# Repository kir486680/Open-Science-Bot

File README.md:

# Open-Science-Bot

ACTIVE DEVELOPMENT

# Introduction
The emerging open science movement provides an opportunity to topple decades of scientific inequity by creating tools that enable engagement in science by underprivileged or marginalized communities. In this movement, scientific data, code, and knowledge, are shared openly in findable, accessible, interoperable, and reusable (F.A.I.R.) forms. However, it is not enough to make software and code available. Scientists need the opportunity to test their hypotheses in a way that increases their understanding while contributing to the broader scientific community.  

Take as an example, electrodeposition which is a method for coating a thin layer of one metal on top of a different metal to modify its surface properties. It is widely used industrially to create corrosion-resistant coatings for automobiles, improve electrical and thermal conductivity in electrical components, and manufacture screens. Optimizing the composition, surface finish, and density of an electroplated alloy is a tedious manual process that involves controlling the concentration of ions and surfactants, the cathodic current, and the temperature of the plating solution. State of the art autonomous deposition tools are currently only possible in well-funded research labs such as at NIST and NRC, where there are active projects within this space.

# Project Description
This research proposes a low-cost and open-source electrochemistry robot. The robot will be a platform for investigating electrochemistry at a price that is suitable for high school science labs but with sufficient precision and extensibility to benefit academic and industrial research.

The following robot has 
- lego xyz stage, which is controlled by Lego Mindstorm Inventor motors and brain, where two motors drive the x and y axes. The motor controlling the y-axis is on the cart carrying the end effectors. The two end effectors of the xyz stage that the cart carries have a gripper, a holder, and a tube connected to a pump. Both end effectors are controlled by another two Lego Mindstorm Inventor motors, and one of them carries the gripper used to grip metal samples and is actuated by a Hitech servo motor. The other end effector carries the reference electrode holder (you have to preinstall them manually), and a tube connected to a pump that pumps electrolytes from the beaker (currently connected to the two beakers).
- another pump connected to the chemical reactor used to drain the reactor after each experiment.
- chemical reactor where the counter electrode is preinstalled, and you are able to submerge the metal sample from the gripper, the preinstalled reference, and pump the liquid which are all held by the end-effector of the xyz stage described above. 
- a metal holder which simply holds the metal samples. 
- potentiostat which is controlled by the software. This is the biggest pain point of the project right now. You need to run the PSPythonSDK/MeasurementExample.py script in palmsdk folder on the windows laptop in order to get the data from the potentiostat. (when you are in the PSPythonSDK folder, just type ```python MeasurementExample.py```). If you want to run the experiment manually, you need to use the PSTrace app on windows. However, also keep in mind that in order to run the potentiostat script you need to use Python 3.8 or below. 

# Example

You can run examples/main.py, which is a preprogrammed sequence that does the following: (Keep in mind that the actual MeasurementExample.py needs to be run separately)
1. Pick up a piece of metal by moving the xyz stage over the metal holder, lower the gripper end effector over the piece of metal, gripping it, and then raise the end effector.
2. The xyz stage will be moved above the reactor, the end effector carrying the pump will be lowered, and the pump will pump some liquid into the reactor.
3. After enough liquid has been pumped into the reactor, the second end effector with the piece of metal will be lowered into the reactor. The experiment will begin.
4. After the experiment, both end effectors will be raised. The second pump will drain the liquid from the reactor.
5. The xyz stage will be moved to a nearby spot to drop off the metal sample. The xyz stage will then be moved back to the (0,0,0) location.

# What is next?

1. You need to be able to somehow call the MeasurementExample.py from the examples/main.py. For that, you might need to setup a server on the raspi using fastapi python package, and also run a server on the windows computer which could execute MeasurementExample.py. I was not able to find a direct way to run the potentiostat from the raspi, but it should be possible... So choose whatever option you think is worth your time.
2. Do active learning. Familiarize yourself with the active_learning/activeLearning.ipynb, and you can use this template code to set up a real system using the robot. The purpose of that demo is to see how you can autonomously find the concentration of electrolyte A and B to achieve a specific goal(in this example the goal is to run an experiment with a peak of 100mV as signified by ```if np.abs(Y_next - 100) < 1: ```)
3. Automate electrolyte replacement in the bath. I have already purchased a pump and Robert will be designing the 3D model for that. 

So what are the specific steps? 

1. find a specific electrochemical experiment that you want to be running(ask prof. Jae for that). Preferrably its some experiment where you are trying to find the ideal peak voltage by changing electrolyte composition.  
2. you can try to manually do data gathering and see if the active learning algorithm guides you in the correct direction. What I mean by manually is to manually run ```python MeasurementExample.py``` or even just use the PSTrace app during the time.sleep while running the ```examples/main.py```. So the workflow woudl be something like this:
    1. run ```python examples/main.py```
    2. during the ```time.sleep(100)``` you can manually run the ```python MeasurementExample.py```(or PSTrace software) to get the data 
    3. Feed this data to the active learning algorithm and make it predict a new concentration of electrolyte A and B
    4. Adjust examples/main.py to pump the amount of electrolyte suggested at the previous step
    5. pour out the liquid from the bath and clean the bath(could be automated).
    6. go back to step 1.

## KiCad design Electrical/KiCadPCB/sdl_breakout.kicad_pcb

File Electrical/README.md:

# Self‑Driving Lab Electronics

*Figure 1 – Breakout PCB, 3‑D view generated in the CAD tool.*

*Figure 2 – As‑built wiring overview of the full electronics stack.*

## General Description
The circuit controls **fluid dosing, sample manipulation, and electrochemical sensing**.  
Two **12 V dosing pumps** are driven through an **L298N dual H‑bridge module**, allowing bidirectional flow control.  
Gripping and mechanical positioning are handled by **two HS‑322HD standard servos**, commanded directly from the Arduino's 5 V logic outputs.  
An **Arduino Uno** serves as the central controller, generating PWM signals for the pumps and servos while streaming experimental parameters to a connected computer.  
Electrochemical measurements are captured by an open‑source **potentiostat module** ([design details on ChemRxiv](https://chemrxiv.org/engage/chemrxiv/article-details/65c436f966c13817292e9bfc)), which receives experiment timing signals (PWM/trigger) from the computer and reports current/voltage data via its own USB/UART interface.  
All point‑to‑point wiring is routed through a **pass‑through breakout PCB** fitted with screw‑terminals and header strips to keep the prototyping area tidy and to simplify hot‑swapping; however, *the breakout board is strictly a convenience layer*—every interconnection shown can be wired directly between the Arduino, driver boards, and sensors without impacting functionality.

## Bill of Materials

| # | Component | Specification / Example Part No. | Qty |
|---|-----------|----------------------------------|----:|
| 1 | Arduino Uno R3 (or compatible) | ATmega328P‑based MCU board | 1 |
| 2 | L298N Dual H‑Bridge Motor Driver Module | 5 V logic, 46 V / 2 A per channel | 1 |
| 3 | 12 V DC Dosing Pump | Peristaltic / diaphragm, ≈0.3 A stall | 2 |
| 4 | Standard Servo Motor | **HS‑322HD**, 5 V supply | 2 |
| 5 | Potentiostat Board | Open‑source design (see ChemRxiv link) | 1 |
| 6 | Breakout / Routing PCB (optional) – BOM at `Electrical/elec/layout/default/production/bom.csv` | Custom 2‑layer FR‑4 with screw‑terminals | 1 |
| 7 | 12 V / 2 A DC Power Supply | Barrel‑jack or Phoenix connector | 1 |
| 8 | Jumper Wires & Dupont Leads | 22 AWG stranded | — |

*Quantities marked "—" depend on enclosure layout.*

### PCB Design Note
The breakout PCB was created with **[Atopile](https://docs.atopile.io/atopile/quickstart)**—a platform that lets you design electronics **with code**. use `sdl_breakout.ato` as the entry to the Atopile project. If you would like to directly submit the PCB files to the manufacturing, use the zip file from `/elec/layout/default/production`

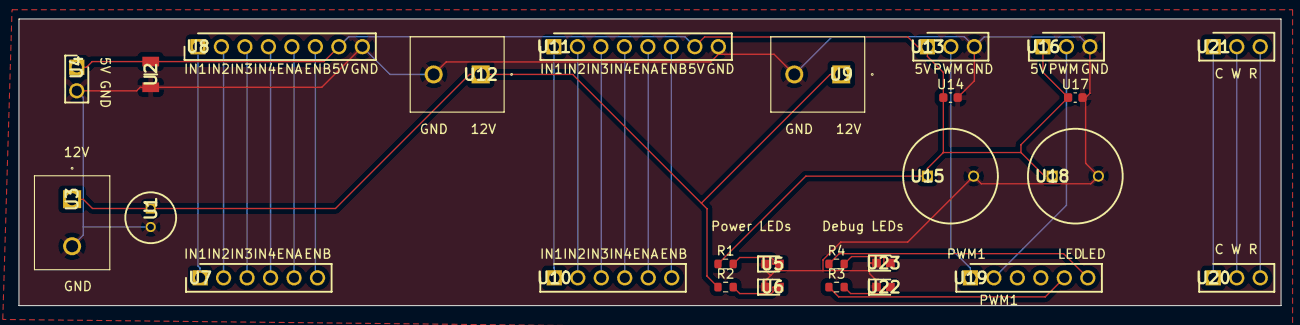
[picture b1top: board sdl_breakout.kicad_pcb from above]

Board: 2 copper layers, 136.5 x 31.0 mm, 27 parts (0 on the bottom side), 26 nets.

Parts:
R1, R3, R4: 100mW Thick Film Resistors 75V ±100ppm/℃ ±1% 390Ω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; R0603
R2: 100mW Thick Film Resistors 75V ±100ppm/℃ ±1% 1.8k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; R0603
U1: Rubycon 100uF 25 V dc Aluminium Electrolytic Capa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; CAPPRD200W50D550H1250
U2: Cap Ceramic 10uF 16V X7R 10% Pad SMD 1206 125C T/R; CAPC3216X180N
U3, U9, U12: PCB terminal block, nominal current: 13.5 A, rate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; 1729128
U4: CONN HEADER VERT 2POS 2.54MM; HDRV2W64P0X254_1X2_508X250X850P
U5, U6, U22, U23: Wurth Elektronik WL-SMCW 520 nm Green LED, 1608 (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; LEDC1608X80N
U7, U10, U19: CONN HEADER VERT 6POS 2.54MM; HDRV6W64P0X254_1X6_1524X250X952P
U8, U11: Conn Unshrouded Header HDR 8 POS 2.54mm Solder ST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; HDRV8W64P0X254_1X8_2032X250X888P
U13, U16, U20, U21: CONN HEADER VERT 3POS 2.54MM; HDRV3W64P0X254_1X3_762X250X952P
U14, U17: SMD Comm X7R, Ceramic, 0.1 uF, 20%, 50 VDC, 125 V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; C0603
U15, U18: Nichicon 470F 25V dc Aluminium Electrolytic Capac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; CAPPRD500W60D1025H1750

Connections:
counter: U20.1, U21.1
debug_led_1.ic-p2: R3.2, U22.2
debug_led_2.ic-p2: R4.2, U23.2
digital5: R3.1, U19.5
digital6: R4.1, U19.6
gnd: U1.2, U2.2, U3.2, U4.2, U5.1, U6.1, U8.8, U9.2, U11.8, U12.2, U13.3, U14.2, U15.2, U16.3, U17.2, U18.2, U22.1, U23.1
motor1-ena: U7.5, U8.5
motor1-enb: U7.6, U8.6
motor1-in1: U7.1, U8.1
motor1-in2: U7.2, U8.2
motor1-in3: U7.3, U8.3
motor1-in4: U7.4, U8.4
motor2-ena: U10.5, U11.5
motor2-enb: U10.6, U11.6
motor2-in1: U10.1, U11.1
motor2-in2: U10.2, U11.2
motor2-in3: U10.3, U11.3
motor2-in4: U10.4, U11.4
power_led_5v.ic-p2: R1.2, U5.2
power_led_12v.ic-p2: R2.2, U6.2
reference: U20.3, U21.3
servo1-control: U13.2, U19.1
servo2-control: U16.2, U19.2
vcc: R2.1, U1.1, U3.1, U9.1, U12.1
vcc-1: R1.1, U2.1, U4.1, U8.7, U11.7, U13.1, U14.1, U15.1, U16.1, U17.1, U18.1
working: U20.2, U21.2

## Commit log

2022-08-13 Added Arduino Code
2022-08-17 Last Commit Before Refactoring
2022-08-18 Kinematics
2022-08-22 Updated calc
2022-08-23 Three Beaker Setup
2022-08-24 Three Beaker Setup Half-automated movement
2022-08-25 Continuing with the automated logic
2022-08-26 Deloading implemented
2022-08-27 Live User Diagnostic
2022-08-27 Gitignore Update
2022-08-27 fixing .gitignore
2022-08-29 New Coord
2022-09-06 Arduino Fix
2023-05-19 update todo in readme
2023-05-19 add whitepaper to readme
2023-05-19 Readme Change
2023-05-19 Fix unit-test-file
2023-05-19 LasestCommit
2023-05-23 New Kinematics
2023-05-25 Fixed Unit Tests
2023-05-25 file struct changed
2023-05-25 init for pump setup
2023-05-25 finish pump code, fix duty cycle and finish calibration
2023-05-26 New FIle Structure
2023-05-26 Fixed UnitTest discovery
2023-05-26 finish camera class
2023-05-26 Changed Gantry Format
2023-05-26 New Pump
2023-05-26 add other files
2023-06-07 Servo Test
2023-06-07 fix documentation errors and type in destructor
2023-06-07 fix camera bugs for get_image
2023-06-07 move initialization into __init__
2023-06-07 init upload for gripper class
2023-06-07 fix imports and tests
2023-06-07 camera + pump + gantry tes
2023-06-08 messy envionment genetation
2023-06-08 requirements generated
2023-06-09 simple multithreading
2023-06-09 More advanced threading
2023-06-09 remove multithreading
2023-06-09 remove tasks
2023-06-12 removed archive
2023-06-12 DevOps improvement
2023-06-12 Update python-app.yml. Remove Lint
2023-06-13 add init for mock classes
2023-06-13 move mock classes into utils folder, add more functions for mock classes
2023-06-13 remove lint for now
2023-06-13 fix requirements
2023-06-13 add gitignore for robot env
2023-06-13 Good
2023-06-13 Will use github issues now
2023-06-13 updated test
2023-06-13 Minor Bug Fixes
2023-06-13 initial upload
2023-06-13 New Gripper Settings
2023-06-13 fix type cast: py3.8 doesnt support union |
2023-06-13 add debug statement
2023-06-13 remove the type checks
2023-06-13 make it ints
2023-06-13 bring back tpye checking bc wasn't the error
2023-06-13 removed bc it was also giving error
2023-06-15 formatting, fix logic errors
2023-06-15 calibrate min/max limits for coordinates
2023-06-15 restore states to default
2023-11-12 Added New Gripper
2023-11-12 Minor Comments
2023-11-14 Simple server comm
2023-11-17 Made it look like a clean package
2023-11-17 Add files
2023-11-17 Fixed broken tests
2023-11-17 Added physical test target
2023-11-19 Fixed make issues and added new target
2024-04-05 fixing bugs
2024-04-23 added some docs
2024-05-03 Improving the doc and adding active learning
2024-05-03 Minor Docs change
2025-01-26 Revamping the repo
2025-01-26 Removing some garbage
2025-01-26 removing cache
2025-01-26 Making code mode efficient
2025-01-26 Minor Tweaks
2025-03-10 Added Parts
2025-03-12 adding electrical stuff
2025-03-12 pushing new electrical and mechanical stuff
2025-03-12 changing name for the pic
2025-03-12 directory shuffle
2025-03-12 Folder Rename
2025-03-12 adding back the folder
2025-03-12 Remove .DS_Store files
2025-04-17 Adding more docs, images, etc...
2025-04-17 more docs/minor robot changes
2025-04-17 adding images
2025-04-17 changing docs
2025-04-17 Adding global readme
2025-04-18 adding docs + pics
2025-04-20 Adding Mechanical Documentation
2025-05-05 Adding new data
2025-05-05 changing readme
2025-05-11 Removed Files and Updated Readme
2025-05-25 Adding Calibration and Bayesian Optimization
2025-05-25 Updating Readme
2025-05-29 cleaning up the files strucuture
2025-06-03 adding new main
2025-06-03 refactoring electrical
2025-06-03 Adding electrical files again
2025-06-03 Adding new image
2025-06-03 removing build 2
2025-06-07 Rename
2025-06-08 Added Printer Mount
2025-06-12 adding new stuff
2025-06-16 fixinf gantry and adding docs
